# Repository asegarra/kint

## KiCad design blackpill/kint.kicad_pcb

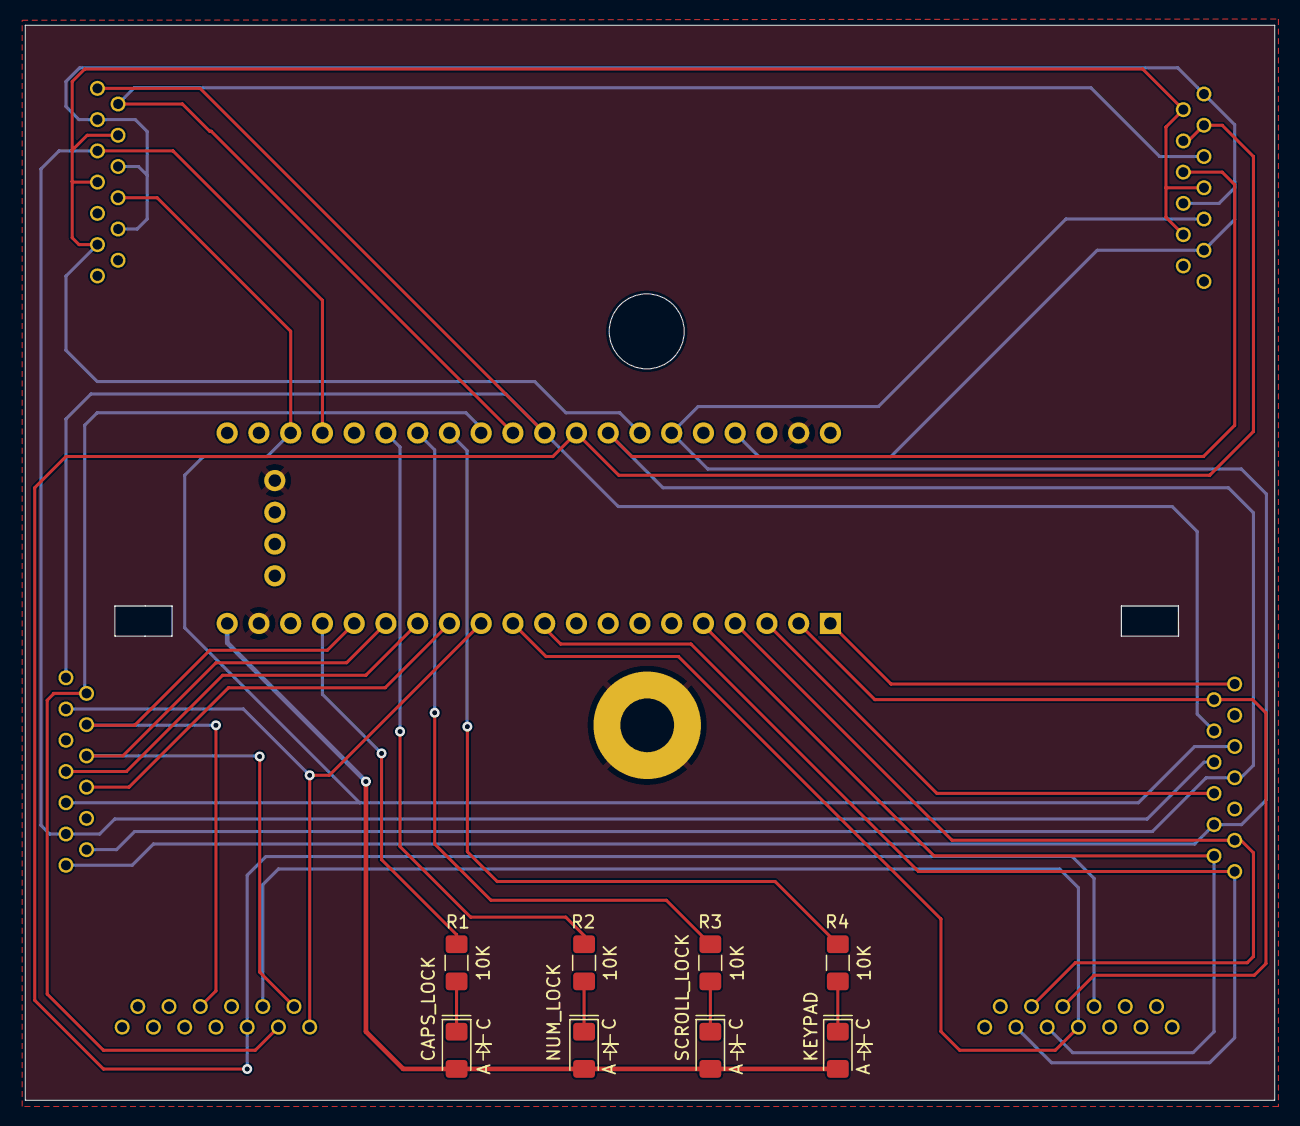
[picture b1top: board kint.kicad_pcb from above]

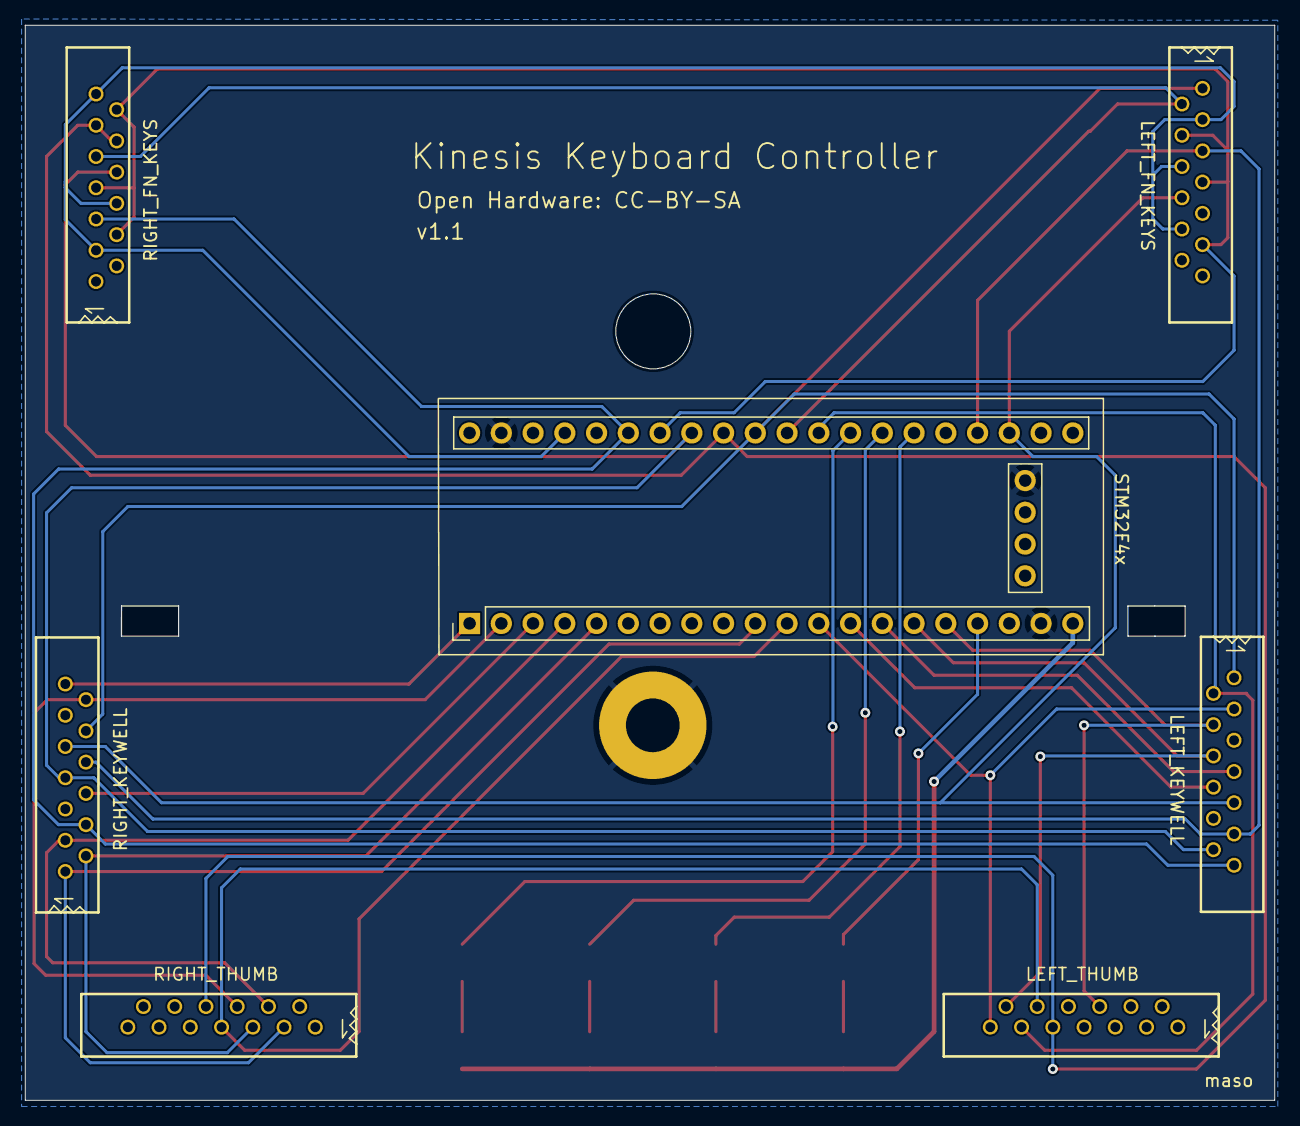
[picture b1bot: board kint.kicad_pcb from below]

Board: 2 copper layers, 99.9 x 86.0 mm, 17 parts (7 on the bottom side), 32 nets.

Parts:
H1: mounting pad; MountingHole_4.3mm_M4_Pad
H2: mounting pad; MountingHole_6mm
J1: RIGHT_THUMB; 39-53-2135
J2: LEFT_KEYWELL; 39-53-2135
J3: LEFT_FN_KEYS; 39-53-2135
J4: RIGHT_FN_KEYS; 39-53-2135
J7: RIGHT_KEYWELL; 39-53-2135
J8: LEFT_THUMB; 39-53-2135
LED1, LED2, LED3, LED4: LEDSML1206; LED_1206_3216Metric_Pad1.42x1.75mm_HandSolder
R1, R2, R3, R4: 10K; R_1206_3216Metric_Pad1.42x1.75mm_HandSolder
U1: YAAJ_WeAct_BlackPill_Part_Like_SWD_Breakout; YAAJ_WeAct_BlackPill_SWD_2

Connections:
/3V3: LED1.2 (A), LED2.2 (A), LED3.2 (A), LED4.2 (A), U1.20 (3V3)
/COL_0: J2.1, J3.1, J7.10, U1.31 (PA5)
/COL_1: J2.9, J3.8, J7.9, U1.23 (PC14)
/COL_2: J2.11, J3.5, J7.8, U1.24 (PC15)
/COL_3: J2.12, J4.8, J7.7, U1.33 (PA7)
/COL_4: J2.13, J4.5, J7.4, U1.35 (PB1)
/COL_5: J1.8, J4.10, J4.11, J8.9, U1.32 (PA6)
/COL_6: J1.7, J8.10, U1.11 (PB3)
/LED_CAPS_LOCK: R1.1, U1.17 (PB9)
/LED_KEYPAD: R4.1, U1.28 (PA2)
/LED_NUM_LOCK: R2.1, U1.26 (PA0)
/LED_SCROLL_LOCK: R3.1, U1.27 (PA1)
/ROW_0: J7.13, U1.1 (PB12)
/ROW_1: J2.7, U1.14 (PB6)
/ROW_2: J2.6, J8.12, U1.15 (PB7)
/ROW_3: J2.4, J8.6, U1.16 (PB8)
/ROW_4: J2.3, J8.13, U1.12 (PB4)
/ROW_5: J2.2, J8.11, U1.29 (PA3)
/ROW_6: J1.3, J7.1, U1.10 (PA15)
/ROW_7: J1.4, J7.3, U1.4 (PB15)
/ROW_8: J1.5, J7.2, U1.5 (PA8)
/ROW_9: J1.6, J7.12, U1.2 (PB13)
/ROW_EQL: J2.8, U1.13 (PB5)
/ROW_ESC: J3.2, J4.9, U1.30 (PA4)
/ROW_F1: J3.3, J3.6, J3.10, J4.3, J4.6, J4.13, U1.37 (PB10)
/ROW_F2: J3.4, J3.7, J3.11, J4.4, J4.7, J4.12, U1.34 (PB0)
/ROW_MIN: J7.6, U1.3 (PB14)
GND: H1.1, U1.19 (GND), U1.39 (GND), U1.41 (GND)
unnamed: LED1.1 (K), R1.2
unnamed: LED2.1 (K), R2.2
unnamed: LED3.1 (K), R3.2
unnamed: LED4.1 (K), R4.2

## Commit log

2025-05-08 remove unused KB500 connectors and move components
2025-05-08 update footprint values
2025-05-08 minor track improveents
2025-05-08 update attributions
2025-05-09 track cleanup
2025-05-11 tracks
2025-05-11 fix fill zone
2025-06-04 Move thumb connectors for less strain on ribbon cables
2025-06-04 Remove silkscreen writing area
2025-06-04 move tracks
2025-06-06 silkscreen updates

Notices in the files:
blackpill/kint.kicad_pcb:
Open Hardware: CC-BY-SA
